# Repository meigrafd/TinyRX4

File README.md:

TinyRX4
=======

RFM12B based TinyRX Receiver for RaspberryPI  

Projekt Page: http://www.forum-raspberrypi.de/Thread-messen-steuern-regeln-batteriebetriebene-funk-sensoren  

## Compiled Sketch size

#### with RFM12B lib:

Receive_PI.ino --> 5.730 Bytes  
Transceiver_PI.ino --> 8.184 Bytes (of 8.192 Bytes)  

#### with JeeLib:

Transceiver_PI_JeeLib.ino --> 7.850 Bytes

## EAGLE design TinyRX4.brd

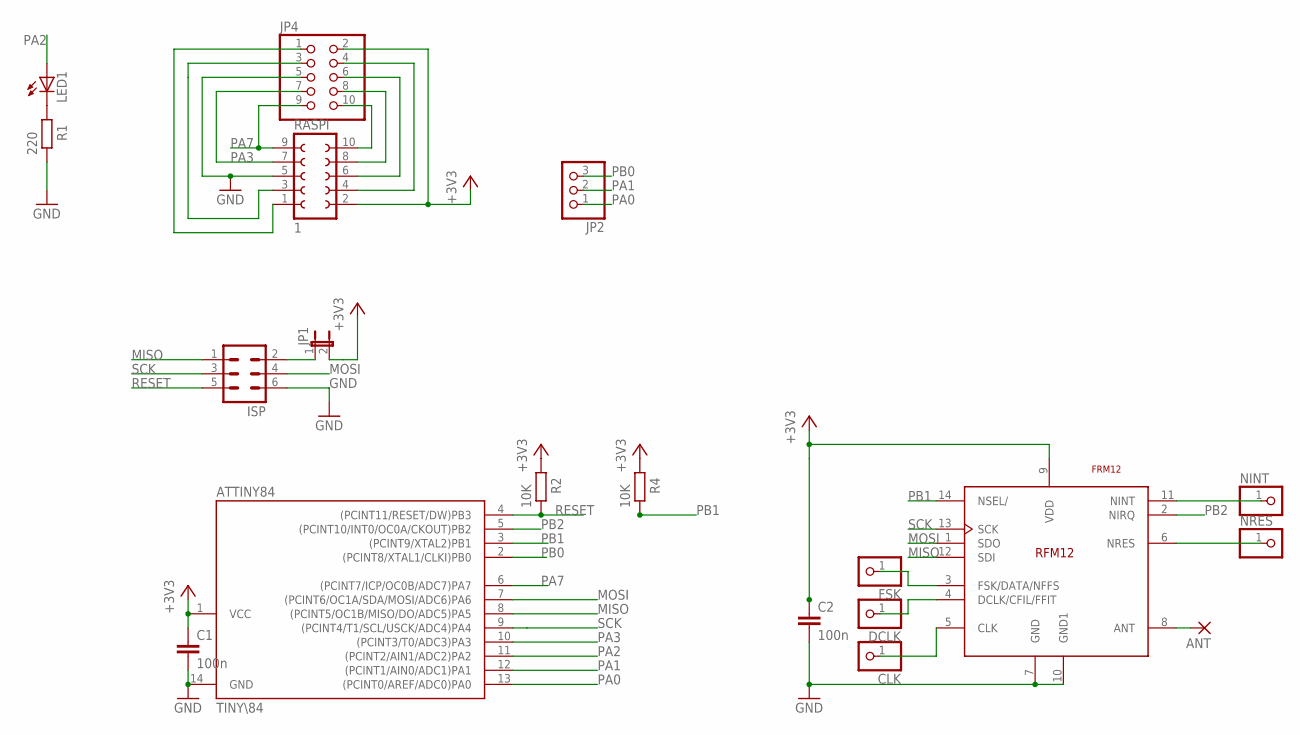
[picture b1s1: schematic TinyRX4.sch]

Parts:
ANT: 1,6/0,8
ATTINY84: TINY\84; SOIC14
C1, C2: 100n; C0805
CLK: PINHD-1X1; 1X01
DCLK: PINHD-1X1; 1X01
FSK: PINHD-1X1; 1X01
ISP: ML6
JP1: JUMPER-2PTH; 1X02
JP2: PINHD-1X3; 1X03
JP4: PINHD-2X5; 2X05
LED1: LEDSML0805; SML0805
NINT: PINHD-1X1; 1X01
NRES: PINHD-1X1; 1X01
R1: 220; R0805
R2, R4: 10K; R0805
RASPI: 1; FE05-2
U$1: FRM12; RFM12

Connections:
+3V3: ATTINY84.1 (VCC), C1.1, C2.1, JP1.2, JP4.2, R2.2, R4.2, RASPI.2, U$1.9 (VDD)
GND: ATTINY84.14 (GND), C1.2, C2.2, ISP.6, JP4.5, R1.1, RASPI.5, U$1.7 (GND), U$1.10 (GND1)
MISO: ATTINY84.8 ((PCINT5/OC1B/MISO/DO/ADC5)PA5), ISP.1, U$1.12 (SDI)
MOSI: ATTINY84.7 ((PCINT6/OC1A/SDA/MOSI/ADC6)PA6), ISP.4, U$1.1 (SDO)
unnamed: ISP.2, JP1.1
unnamed: JP4.10, RASPI.10
unnamed: LED1.C, R1.2
unnamed: JP4.8, RASPI.8
unnamed: JP4.6, RASPI.6
unnamed: ANT.1, U$1.8 (ANT)
unnamed: JP4.4, RASPI.4
unnamed: JP4.1, RASPI.1
unnamed: JP4.3, RASPI.3
unnamed: NINT.1, U$1.11 (NINT)
unnamed: CLK.1, U$1.5 (CLK)
unnamed: DCLK.1, U$1.4 (DCLK/CFIL/FFIT)
unnamed: NRES.1, U$1.6 (NRES)
unnamed: FSK.1, U$1.3 (FSK/DATA/NFFS)
PA0: ATTINY84.13 ((PCINT0/AREF/ADC0)PA0), JP2.1
PA1: ATTINY84.12 ((PCINT1/AIN0/ADC1)PA1), JP2.2
PA2: ATTINY84.11 ((PCINT2/AIN1/ADC2)PA2), LED1.A
PA3: ATTINY84.10 ((PCINT3/T0/ADC3)PA3), JP4.7, RASPI.7
PA7: ATTINY84.6 ((PCINT7/ICP/OC0B/ADC7)PA7), JP4.9, RASPI.9
PB0: ATTINY84.2 ((PCINT8/XTAL1/CLKI)PB0), JP2.3
PB1: ATTINY84.3 ((PCINT9/XTAL2)PB1), R4.1, U$1.14 (NSEL/)
PB2: ATTINY84.5 ((PCINT10/INT0/OC0A/CKOUT)PB2), U$1.2 (NIRQ)
RESET: ATTINY84.4 ((PCINT11/RESET/DW)PB3), ISP.5, R2.1
SCK: ATTINY84.9 ((PCINT4/T1/SCL/USCK/ADC4)PA4), ISP.3, U$1.13 (SCK)

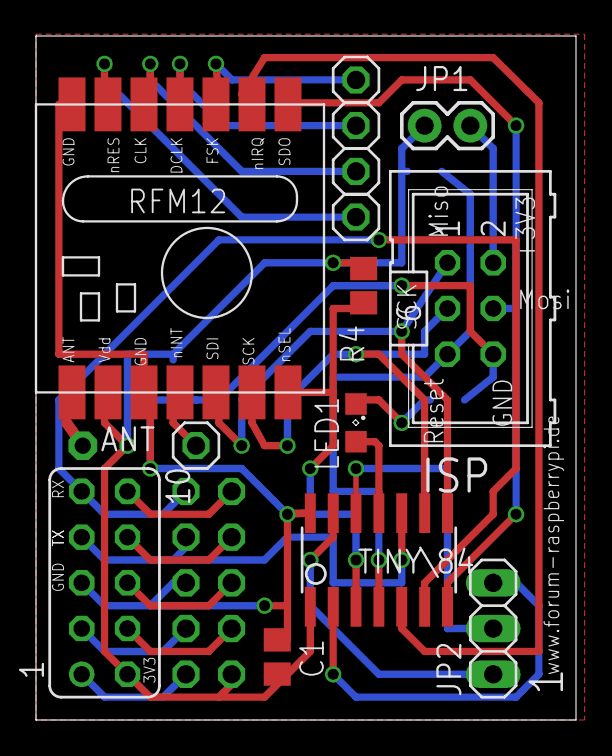
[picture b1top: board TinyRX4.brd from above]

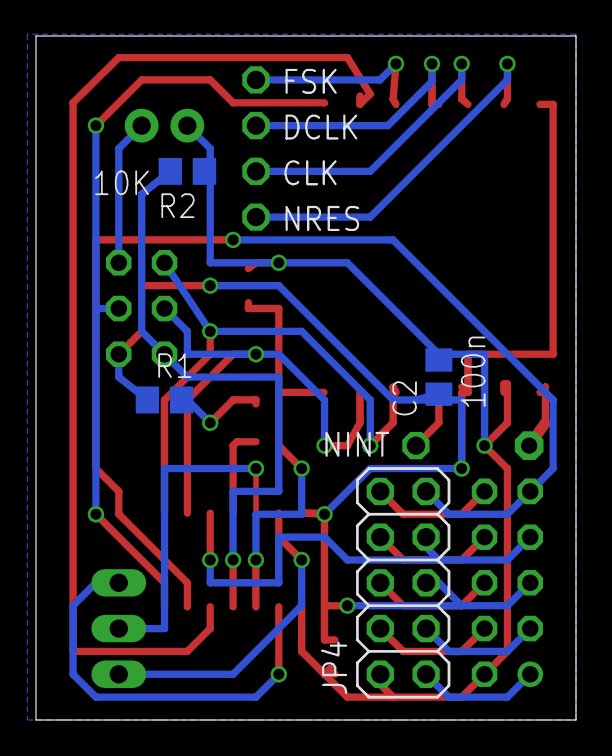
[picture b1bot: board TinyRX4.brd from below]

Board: 2 copper layers, 30.0 x 38.0 mm, 19 parts (4 on the bottom side), 28 nets.

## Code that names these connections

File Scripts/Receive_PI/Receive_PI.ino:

// RFM12B Receiver for RaspberryPI
//
// Basiert zum Teil auf der Arbeit von Nathan Chantrell
//
// modified by meigrafd @ 16.12.2013 - for UART on RaspberryPI
//------------------------------------------------------------------------------
#include <RFM12B.h>
#include <avr/sleep.h>
#include <SoftwareSerial.h>
//------------------------------------------------------------------------------
// You will need to initialize the radio by telling it what ID it has and what network it's on
// The NodeID takes values from 1-127, 0 is reserved for sending broadcast messages (send to all nodes)
// The Network ID takes values from 0-255
// By default the SPI-SS line used is D10 on Atmega328. You can change it by calling .SetCS(pin) where pin can be {8,9,10}
#define NODEID            22  //network ID used for this unit
#define NETWORKID        210  //the network ID we are on
#define ACK_TIME        2000  // # of ms to wait for an ack
#define SERIAL_BAUD     9600
//------------------------------------------------------------------------------
// PIN-Konfiguration 
//------------------------------------------------------------------------------
// UART pins
#define rxPin 7 // D7, PA3
#define txPin 3 // D3, PA7. pin der an RXD vom PI geht.
// LED pin
#define LEDpin 8 // D8, PA2 - set to 0 to disable LED
/*
                     +-\/-+
               VCC  1|    |14  GND
          (D0) PB0  2|    |13  AREF (D10)
          (D1) PB1  3|    |12  PA1 (D9)
             RESET  4|    |11  PA2 (D8)
INT0  PWM (D2) PB2  5|    |10  PA3 (D7)
      PWM (D3) PA7  6|    |9   PA4 (D6)
      PWM (D4) PA6  7|    |8   PA5 (D5) PWM
                     +----+
*/

//encryption is OPTIONAL
//to enable encryption you will need to:
// - provide a 16-byte encryption KEY (same on all nodes that talk encrypted)
// - to call .Encrypt(KEY) to start en
// - to stop encrypting call .Encrypt(NULL)
//#define KEY   "ABCDABCDABCDABCD"

// Initialise UART
SoftwareSerial mySerial(rxPin, txPin);

// Need an instance of the Radio Module
RFM12B radio;

//##############################################################################

static void activityLED (byte mode) {
  pinMode(LEDpin, OUTPUT);
  digitalWrite(LEDpin, mode);
}

// blink led
static void blink (byte pin, byte n = 3) {
  pinMode(pin, OUTPUT);
  for (byte i = 0; i < 2 * n; ++i) {
    delay(100);
    digitalWrite(pin, !digitalRead(pin));
  }
}

// init Setup
void setup() {
  pinMode(rxPin, INPUT);
  pinMode(txPin, OUTPUT);
  mySerial.begin(SERIAL_BAUD);
  radio.Initialize(NODEID, RF12_433MHZ, NETWORKID);
  #ifdef KEY
    radio.Encrypt((byte*)KEY);      //comment this out to disable encryption
  #endif
  if (LEDpin) {
    activityLED(1); // LED on
    delay(1000);
    activityLED(0); // LED off
  }
}

// Loop
void loop() {
  if (radio.ReceiveComplete()) {
    if (radio.CRCPass()) {
      //node ID of TX, extracted from RF datapacket. Not transmitted as part of structure
      mySerial.print(radio.GetSender(), DEC);
      mySerial.print(" ");
      int i;
      for (byte i = 0; i < *radio.DataLen; i++) //can also use radio.GetDataLen() if you don't like pointers
        mySerial.print((char) radio.Data[i]);

      if (LEDpin) {
        blink(LEDpin, 2);
      }
      if (radio.ACKRequested()) {
        radio.SendACK();
        mySerial.print(" - ACK sent");
      }
    } else {
      mySerial.print("BAD-CRC");
      if (LEDpin) {
        activityLED(1); // LED on
        delay(1000);
        activityLED(0); // LED off
      }
    }
    mySerial.println();
  }
}

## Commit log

2014-03-07 Public build
2015-01-23 Added Sensor.pl and Receiver_PI.ino
2015-01-23 moved
2015-01-31 Added Web part. v0.61
2015-01-31 Added watchdog_Sensor.sh for Sensor.pl
2015-02-01 Transceiver functionality added
    receiving data from nodes and can transmit special data to specified
    node with syntax SENDTOID:message
2015-02-04 Screenshot added
